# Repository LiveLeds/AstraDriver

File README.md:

# AstraDriver

[GitHub IO Page](https://liveleds.github.io/AstraDriver)

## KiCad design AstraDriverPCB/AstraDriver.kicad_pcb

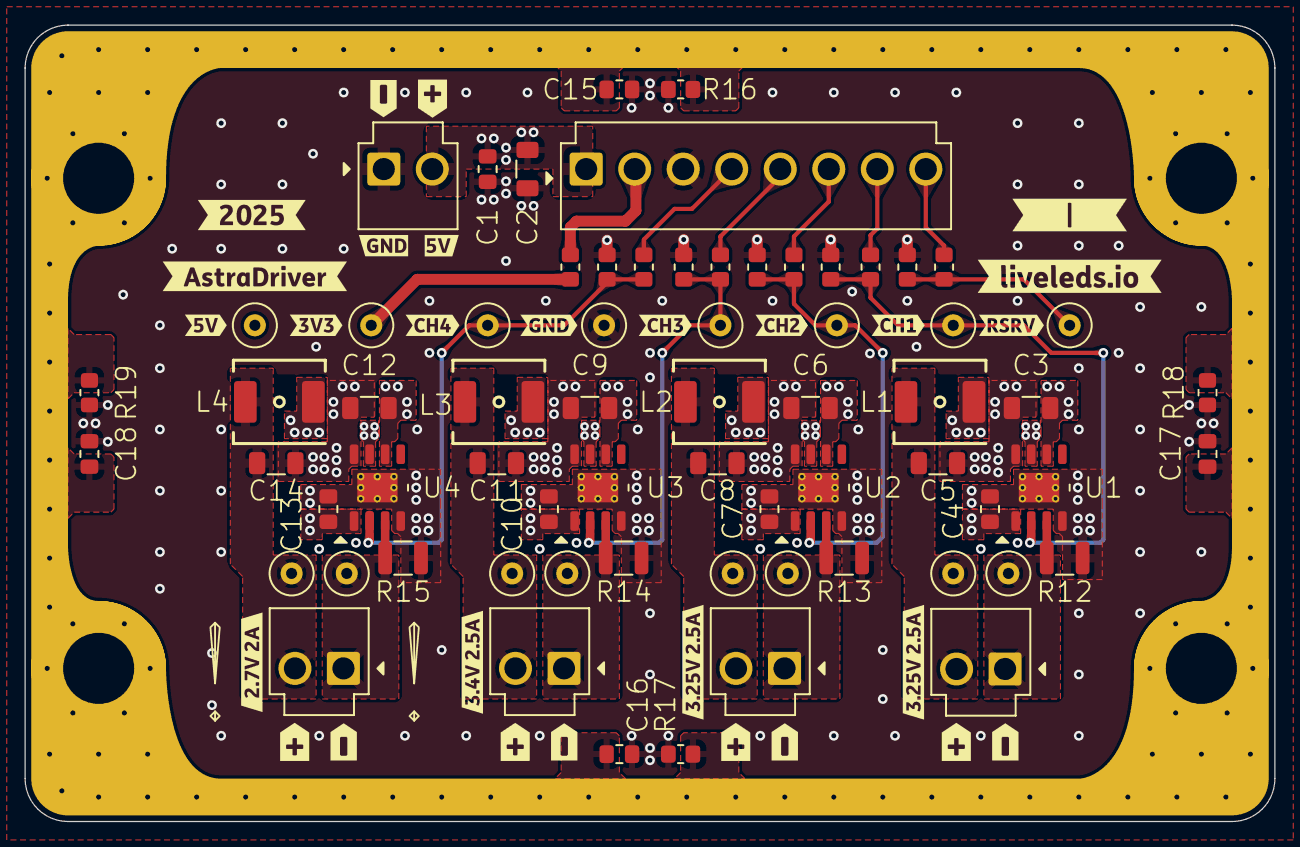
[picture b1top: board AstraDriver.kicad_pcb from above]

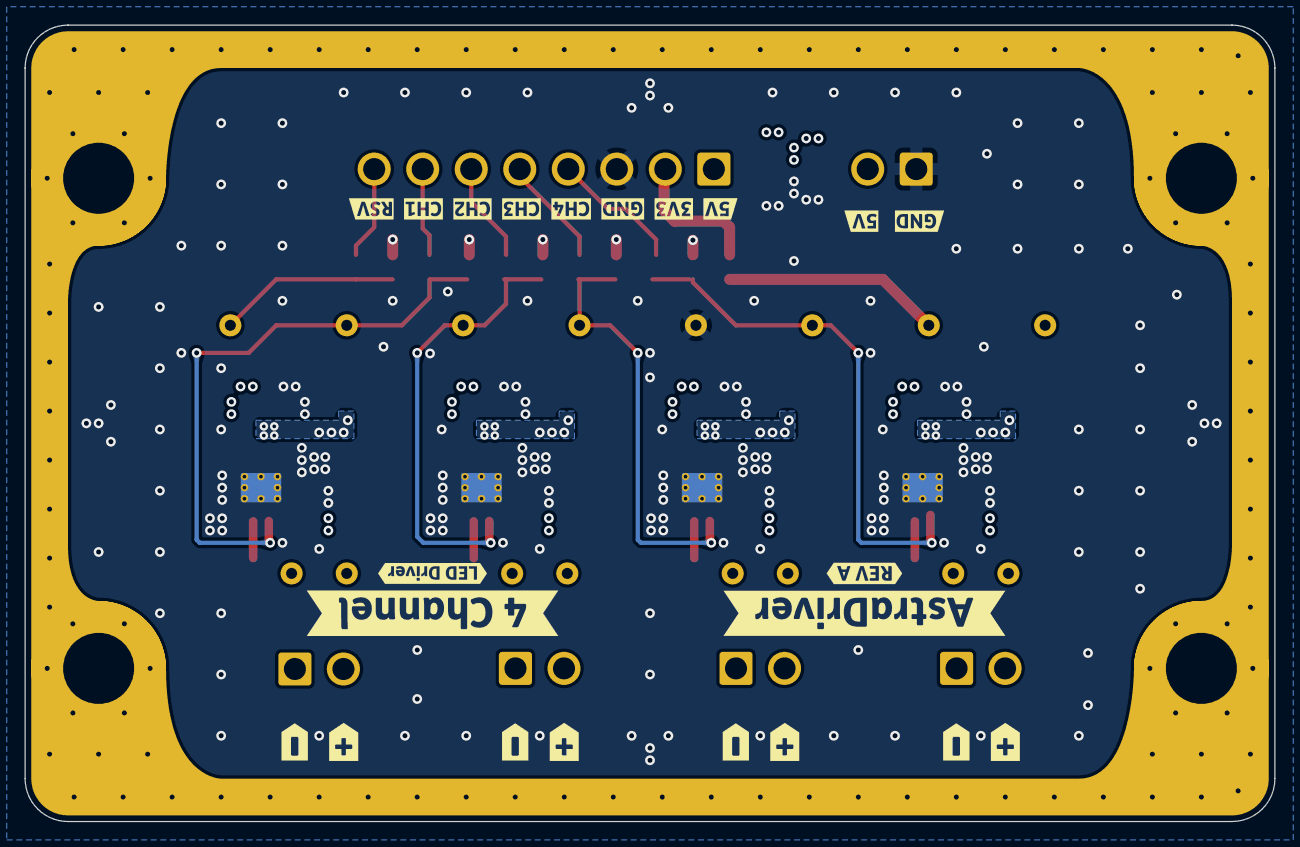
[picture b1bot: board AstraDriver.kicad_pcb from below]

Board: 4 copper layers, 102.0 x 65.0 mm, 118 parts (22 on the bottom side), 27 nets.

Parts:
C1: DNP; C_DNP_0805_2012Metric_Pad1.18x1.45mm_HandSolder
C2: 100u; C_1206_3216Metric_Pad1.33x1.80mm_HandSolder
C3, C6, C9, C12: 22u; C_1206_3216Metric_Pad1.33x1.80mm_HandSolder
C4, C7, C10, C13: 1u; C_0805_2012Metric_Pad1.18x1.45mm_HandSolder
C5, C8, C11, C14: 4u7; C_1206_3216Metric_Pad1.33x1.80mm_HandSolder
C15, C16, C17, C18: 10n; C_0805_2012Metric_Pad1.18x1.45mm_HandSolder
CN1: JST VH 8 PIN (CLONE); JST_VH_CLONE_B8P-VH-B_1x08_P3.96mm_Vertical
CN2, CN3, CN4, CN5, CN6: JST VH 2 PIN; JST_VH_B2P-VH-B_1x02_P3.96mm_Vertical
L1, L2, L3, L4: 2u2H; L_TDK_SPM6530T-2R2M
R1, R2, R3, R4, R5, R6: 0; R_0805_2012Metric_Pad1.20x1.40mm_HandSolder
R7, R8, R9, R10, R11: 10k; R_0805_2012Metric_Pad1.20x1.40mm_HandSolder
R12, R13, R14: 40m; R_1210_3225Metric
R15: 47m; R_1210_3225Metric
R16: 1M; R_0805_2012Metric_Pad1.20x1.40mm_HandSolder
R17, R18, R19: DNP; R_DNP_0805_2012Metric_Pad1.20x1.40mm_HandSolder
RING1: AstraDriver_Ground_Ring
TP1, TP2, TP3, TP4, TP5, TP6, TP7, TP8, TP9, TP10, TP11, TP12, TP13, TP14, TP15, TP16: TestPoint_Thimble; TestPoint_Loop_D3.50mm_Drill0.9mm_Beaded
U1, U2, U3, U4: LED2001PHR; U_LED2001PHR_HSOP8
kibuzzard-67ACE9FE: G***; kibuzzard-67ACE9FE
kibuzzard-67ACEA04: G***; kibuzzard-67ACEA04
kibuzzard-67B0BCB5: G***; kibuzzard-67B0BCB5
kibuzzard-67B1DE0F: G***; kibuzzard-67B1DE0F
kibuzzard-67B1DE14: G***; kibuzzard-67B1DE14
kibuzzard-67B1DE99, kibuzzard-67B1DE99#2, kibuzzard-67B1DE99#3, kibuzzard-67B1DE99#4: G***; kibuzzard-67B1DE99
kibuzzard-67B1DEA2, kibuzzard-67B1DEA2#2, kibuzzard-67B1DEA2#3, kibuzzard-67B1DEA2#4: G***; kibuzzard-67B1DEA2
kibuzzard-67B1DFB0: G***; kibuzzard-67B1DFB0
kibuzzard-67B1DFC8: G***; kibuzzard-67B1DFC8
kibuzzard-67EB9EA5: G***; kibuzzard-67EB9EA5
kibuzzard-67EB9FE0: G***; kibuzzard-67EB9FE0
kibuzzard-67263EBF: G***; kibuzzard-67263EBF
kibuzzard-67263F1F: G***; kibuzzard-67263F1F
kibuzzard-67263F3C: G***; kibuzzard-67263F3C
kibuzzard-67263F3F: G***; kibuzzard-67263F3F
kibuzzard-67263F8C: G***; kibuzzard-67263F8C
kibuzzard-67263F35: G***; kibuzzard-67263F35
kibuzzard-67263F87: G***; kibuzzard-67263F87
kibuzzard-67264EAC: G***; kibuzzard-67264EAC
kibuzzard-67264F3E: G***; kibuzzard-67264F3E
kibuzzard-67264F60: G***; kibuzzard-67264F60
kibuzzard-67264F65: G***; kibuzzard-67264F65
kibuzzard-67609A4F: G***; kibuzzard-67609A4F
kibuzzard-67609A54: G***; kibuzzard-67609A54
kibuzzard-67609A62: G***; kibuzzard-67609A62
kibuzzard-67718F9D: G***; kibuzzard-67718F9D
kibuzzard-67718FA4: G***; kibuzzard-67718FA4
kibuzzard-672647E1: G***; kibuzzard-672647E1
kibuzzard-676095B5: G***; kibuzzard-676095B5
kibuzzard-676095BC: G***; kibuzzard-676095BC
kibuzzard-676095C8: G***; kibuzzard-676095C8
kibuzzard-676095D3: G***; kibuzzard-676095D3
kibuzzard-6726414E, kibuzzard-6726414E#2, kibuzzard-6726414E#3, kibuzzard-6726414E#4, kibuzzard-6726414E#5: G***; kibuzzard-6726414E
kibuzzard-6760963B: G***; kibuzzard-6760963B
kibuzzard-67264157, kibuzzard-67264157#2, kibuzzard-67264157#3, kibuzzard-67264157#4, kibuzzard-67264157#5: G***; kibuzzard-67264157
kibuzzard-67609643: G***; kibuzzard-67609643

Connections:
+3V3: R6.2, TP4.1
+5V: C1.2, C2.2, C3.2, C4.2, C6.2, C7.2, C9.2, C10.2, C12.2, C13.2, CN1.1, CN2.2, TP3.1, U1.1 (VINA), U1.6 (VINSW), U2.1 (VINA), U2.6 (VINSW), U3.1 (VINA), U3.6 (VINSW), U4.1 (VINA), U4.6 (VINSW)
/Block Diagram/3V3_R: CN1.2, R6.1
/Block Diagram/CH1_LED+: C5.2, CN6.2, L1.2, TP16.1
/Block Diagram/CH1_LED-: CN6.1, R12.2, TP15.1, U1.3 (FB)
/Block Diagram/CH2_LED+: C8.2, CN5.2, L2.2, TP14.1
/Block Diagram/CH2_LED-: CN5.1, R13.2, TP13.1, U2.3 (FB)
/Block Diagram/CH3_LED+: C11.2, CN4.2, L3.2, TP12.1
/Block Diagram/CH3_LED-: CN4.1, R14.2, TP11.1, U3.3 (FB)
/Block Diagram/CH4_LED+: C14.2, CN3.2, L4.2, TP10.1
/Block Diagram/CH4_LED-: CN3.1, R15.2, TP9.1, U4.3 (FB)
/Block Diagram/Channel 1 Blue and CY 2.5A/SW_OUT: L1.1, U1.7 (SW)
/Block Diagram/Channel 2 Blue and CY 2.5A/SW_OUT: L2.1, U2.7 (SW)
/Block Diagram/Channel 3 Green 2.5A/SW_OUT: L3.1, U3.7 (SW)
/Block Diagram/Channel 4 Red 2A/SW_OUT: L4.1, U4.7 (SW)
/Block Diagram/DIM_1: R4.2, R11.2, TP8.1, U1.2 (DIM)
/Block Diagram/DIM_2: R3.2, R10.2, TP7.1, U2.2 (DIM)
/Block Diagram/DIM_3: R2.2, R9.2, TP6.1, U3.2 (DIM)
/Block Diagram/DIM_4: R1.2, R8.2, TP5.1, U4.2 (DIM)
/Block Diagram/PWM_CH1: CN1.7, R4.1
/Block Diagram/PWM_CH2: CN1.6, R3.1
/Block Diagram/PWM_CH3: CN1.5, R2.1
/Block Diagram/PWM_CH4: CN1.4, R1.1
/Block Diagram/RESERVED: CN1.8, R5.1
/Block Diagram/RSRV: R5.2, R7.2, TP2.1
CHASSIS: C15.2, C16.2, C17.2, C18.2, R16.2, R17.2, R18.2, R19.2, RING1.1 (2)
GND: C1.1, C2.1, C3.1, C4.1, C5.1, C6.1, C7.1, C8.1, C9.1, C10.1, C11.1, C12.1, C13.1, C14.1, C15.1, C16.1, C17.1, C18.1, CN1.3, CN2.1, R7.1, R8.1, R9.1, R10.1, R11.1, R12.1, R13.1, R14.1, R15.1, R16.1, R17.1, R18.1, R19.1, TP1.1, U1.4 (AGND), U1.8 (PGND), U1.9 (EP), U2.4 (AGND), U2.8 (PGND), U2.9 (EP), U3.4 (AGND), U3.8 (PGND), U3.9 (EP), U4.4 (AGND), U4.8 (PGND), U4.9 (EP)

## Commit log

2024-10-06 Correct pcb and schematic
2024-10-06 Update board dimensions and center
2024-10-06 Enabled github pages
2024-10-07 Progress
2024-10-07 Cleanup
2024-10-11 Added all schematic components
2024-10-15 Finished layout
2024-10-15 Added extra caps, cleanup
2024-11-02 Finished silkscreen and board
2024-11-02 DFM fixes
2024-11-02 Create render
2024-11-02 Reduce samples
2024-11-02 More dfm
2024-11-02 Add step file and tweak top angled 3d
2024-11-02 Tweaks
2024-11-02 Updated step filename
2024-11-02 Fix step
2024-11-02 Improve 3d angled render
2024-11-02 Update for kiri
2024-11-02 Tweak angled render
2024-11-03 HQ Render
2024-11-03 Update size
2024-11-04 New render
2024-12-15 New layout in progress
2024-12-16 Finished layout and silkscreen, and stitching
2024-12-18 Prepare for review, cleanup
2024-12-18 Tweaks for JLC
2024-12-18 Fix index update top angled
2024-12-18 Fix top angled
2024-12-18 Fix top angled again
2024-12-18 Tweak renders
2024-12-18 Tweak renders and 100 samples
2024-12-20 1 sample
2024-12-20 Some via tweaks
2024-12-20 Fix drc erc report
2024-12-20 Fix preflight drc erc
2024-12-20 Tweak vias
2024-12-20 Tweak top angled render
2024-12-20 Fix fab
2024-12-30 Added another 2 PIN VH connector for power, cleanup
2025-02-09 Rough layout
2025-02-09 2 samples
2025-02-15 Relayout
2025-02-16 Layout complete
2025-02-16 Fix renders
2025-02-16 Fix scale
2025-02-16 Add dxf for ring
2025-02-16 reduce scale
2025-02-16 Increase factor
2025-04-01 SLK tweaks
2025-04-01 Update vh to clone
2025-04-04 Fix bad pour after teardrops
2025-04-04 Updated thermal spokes
2025-04-04 Updated dimensions
2025-04-04 Larger area for led power connectors
2025-04-04 Increase inductor connection
2025-06-29 Add post delivery description
2025-06-29 fix images dir -p in ci.yml
2025-06-29 Fix top angled render
2025-06-29 Fix clipping
2025-06-29 Reduce light
2025-06-29 100 samples
2025-07-08 Added angled top picture
